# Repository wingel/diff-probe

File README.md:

What is different in this fork?
===============================
* KiCAD version of only the tested B variant
* Board slightly optimized (NF resistors removed)
* JLCPCB production files added (with assembly)

An almost GHZ active differential probe
=======================================

This is the design for an active differential probe which has a
bandwidth of about 800MHz and which is useful to beyond 1GHz.

I have written some articles about the probe:
[Part&nbsp;1](http://blog.weinigel.se/2016/02/26/ghz-differential-probe.html),
[Part&nbsp;2](http://blog.weinigel.se/2016/02/28/ghz-differential-probe-2.html), and
[Part&nbsp;3](http://blog.weinigel.se/2016/03/16/ghz-differential-probe-3.html).

A few notes
===========

So far I have only built the B variant of the probe, that is, the
probe with separate OP amps for the inputs.

On variant B, the input resistors R20/R21, R28/R29 and output
resistors R30/R31 are arranged in such a way that one can use just one
resistor between the input of the first resistor to the output of the
second resistor.  That's why it says "0Ω/NF" on one of the resistors
in both pairs.

The image in [S21ProbeBW_1.png](S21ProbeBW_1.png) shows a plot of the
frequency response for variant B using LMH6702 OP-AMPs, 150Ω on R20
and R28, 220Ω on R26, R27, R37 and R38 and 1.1k on R22 and R32.  Note
that the 150Ω resistors were mounted across R20/R21 and R28/R29 and
the and 50Ω matching resistor for the output was mounted across
R30/R31.  The power supply with a LMH6702 OP-AMPs should be about 5V
and the probe should be able to measure signals up to about +/-3.3V.

If you want the probe input to be AC coupled you can mount the input
resistor in its proper position on R20 and R28 and mount a capacitor
(0.1µF might be a good starting value) on R21 and R29.  You can also
AC couple the output by mounting the 50Ω matching resistor on R30 and
a another small capacitor on R31.

License
=======

[diff-probe](https://github.com/wingel/diff-probe) by
[Christer Weinigel](mailto:christer@weinigel.se) is licensed under a
[Creative Commons Attribution 4.0 International
License](http://creativecommons.org/licenses/by/4.0/).

The intent is to make this PCB available to anyone that finds it
useful as long as I get credit for the original design.  If you want
to use the design and have issues with the above license, please
contact me.

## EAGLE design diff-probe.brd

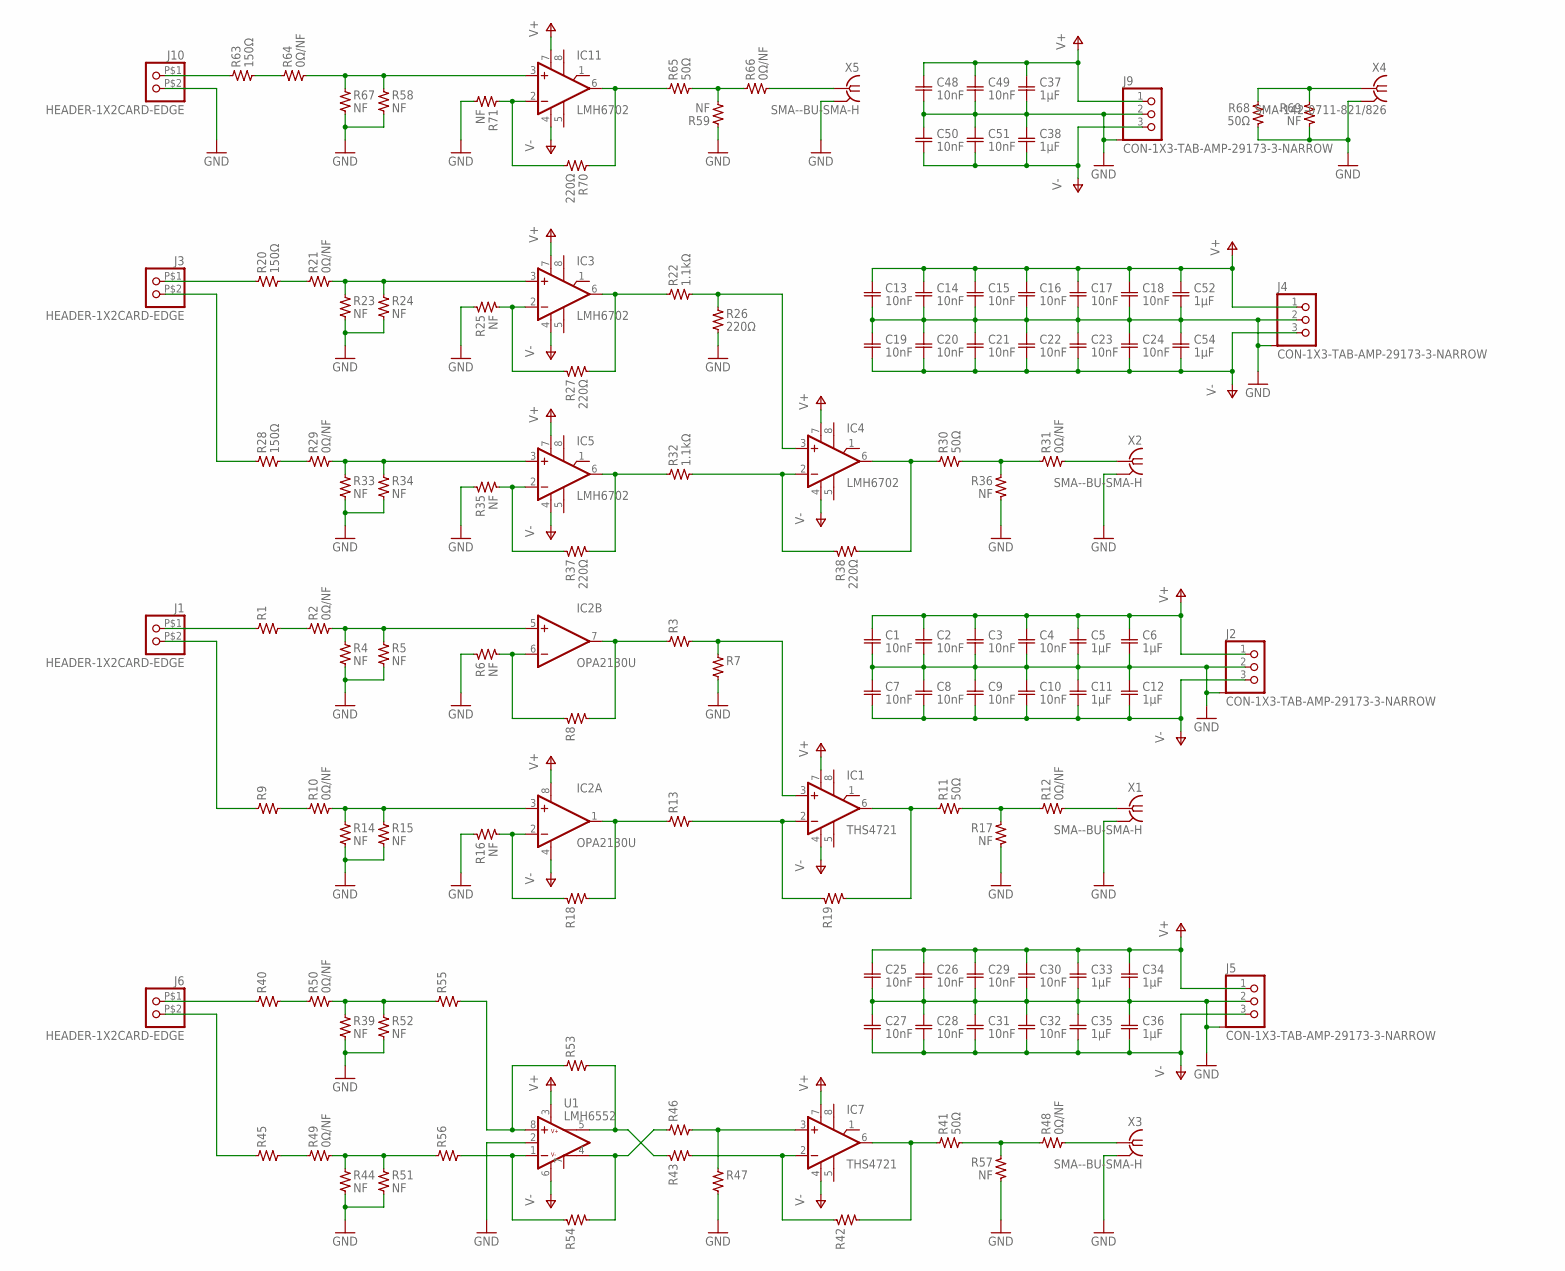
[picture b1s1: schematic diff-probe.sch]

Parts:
C1, C2, C3, C4, C7, C8, C9, C10, C13, C14, C15, C16, C17, C18, C19, C20, C21, C22, C23, C24, C25, C26, C27, C28, C29, C30, C31, C32, C48, C49, C50, C51: 10nF; 0402-SQUARE
C5, C6, C11, C12, C33, C34, C35, C36, C37, C38: 1µF; 0603-SQUARE
C52, C54: 1µF; 0603
IC1, IC7: THS4721; SO08
IC2: OPA2130U; SO08
IC3, IC4, IC5, IC11: LMH6702; SO08
J1, J3, J6, J10: HEADER-1X2CARD-EDGE; CARD_EDGE_PADS-1X2
J2, J4, J5, J9: CON-1X3-TAB-AMP-29173-3-NARROW; AMP-29173-3-NARROW
R1, R3, R7, R8, R9, R13, R18, R19, R40, R42, R43, R45, R46, R47, R53, R54, R55, R56: R-US-0402-SQUARE; 0402-SQUARE
R2, R10, R12, R21, R29, R31, R48, R49, R50, R64, R66: 0Ω/NF; 0402-SQUARE
R4, R5, R6, R14, R15, R16, R17, R23, R24, R25, R33, R34, R35, R36, R39, R44, R51, R52, R57, R58, R59, R67, R71: NF; 0402-SQUARE
R11, R30, R41, R65, R68: 50Ω; 0402-SQUARE
R20, R28, R63: 150Ω; 0402-SQUARE
R22, R32: 1.1kΩ; 0402-SQUARE
R26, R27, R37, R38, R70: 220Ω; 0402-SQUARE
R69: NF; 0603-SQUARE
U1: LMH6552; SO08
X1, X2, X3, X5: SMA--BU-SMA-H; BU-SMA-H
X4: SMA-142-0711-821/826; J502-ND-142-0711-821/826

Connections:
GND: C1.P$2 (2), C2.P$2 (2), C3.P$2 (2), C4.P$2 (2), C5.2, C6.2, C7.P$1 (1), C8.P$1 (1), C9.P$1 (1), C10.P$1 (1), C11.1, C12.1, C13.P$2 (2), C14.P$2 (2), C15.P$2 (2), C16.P$2 (2), C17.P$2 (2), C18.P$2 (2), C19.P$1 (1), C20.P$1 (1), C21.P$1 (1), C22.P$1 (1), C23.P$1 (1), C24.P$1 (1), C25.P$2 (2), C26.P$2 (2), C27.P$1 (1), C28.P$1 (1), C29.P$2 (2), C30.P$2 (2), C31.P$1 (1), C32.P$1 (1), C33.2, C34.2, C35.1, C36.1, C37.2, C38.1, C48.P$2 (2), C49.P$2 (2), C50.P$1 (1), C51.P$1 (1), C52.2, C54.1, J2.2, J2.P$4, J2.P$5, J4.2, J4.P$4, J4.P$5, J5.2, J5.P$4, J5.P$5, J9.2, J9.P$4, J9.P$5, J10.P$2 (2), R4.P$2 (2), R5.P$2 (2), R6.P$1 (1), R7.P$2 (2), R14.P$2 (2), R15.P$2 (2), R16.P$1 (1), R17.P$2 (2), R23.P$2 (2), R24.P$2 (2), R25.P$1 (1), R26.P$2 (2), R33.P$2 (2), R34.P$2 (2), R35.P$1 (1), R36.P$2 (2), R39.P$2 (2), R44.P$2 (2), R47.P$2 (2), R51.P$2 (2), R52.P$2 (2), R57.P$2 (2), R58.P$2 (2), R59.P$1 (1), R67.P$2 (2), R68.P$2 (2), R69.2, R71.P$2 (2), U1.2 (VCM), X1.2, X1.3 (2), X1.4 (2), X1.5 (2), X2.2, X2.3 (2), X2.4 (2), X2.5 (2), X3.2, X3.3 (2), X3.4 (2), X3.5 (2), X4.G@1 (2), X4.G@2 (2), X4.G@3 (2), X4.G@4 (2), X5.2, X5.3 (2), X5.4 (2), X5.5 (2)
unnamed: IC11.3 (+IN), R58.P$1 (1), R64.P$2 (2), R67.P$1 (1)
unnamed: R63.P$2 (2), R64.P$1 (1)
unnamed: J10.P$1 (1), R63.P$1 (1)
unnamed: R59.P$2 (2), R65.P$2 (2), R66.P$1 (1)
unnamed: IC11.6 (OUT), R65.P$1 (1), R70.P$1 (1)
unnamed: R66.P$2 (2), X5.1
unnamed: R53.P$1 (1), R55.P$2 (2), U1.8 (+IN)
unnamed: R40.P$2 (2), R50.P$1 (1)
unnamed: R43.P$1 (1), R53.P$2 (2), U1.5 (-OUT)
unnamed: R41.P$2 (2), R48.P$1 (1), R57.P$1 (1)
unnamed: IC7.6 (OUT), R41.P$1 (1), R42.P$2 (2)
unnamed: IC7.2 (-IN), R42.P$1 (1), R43.P$2 (2)
unnamed: R39.P$1 (1), R50.P$2 (2), R52.P$1 (1), R55.P$1 (1)
unnamed: R45.P$2 (2), R49.P$1 (1)
unnamed: R46.P$1 (1), R54.P$2 (2), U1.4 (+OUT)
unnamed: IC7.3 (+IN), R46.P$2 (2), R47.P$1 (1)
unnamed: J6.P$1 (1), R40.P$1 (1)
unnamed: J6.P$2 (2), R45.P$1 (1)
unnamed: R48.P$2 (2), X3.1
unnamed: R54.P$1 (1), R56.P$2 (2), U1.1 (-IN)
unnamed: R44.P$1 (1), R49.P$2 (2), R51.P$1 (1), R56.P$1 (1)
unnamed: IC11.2 (-IN), R70.P$2 (2), R71.P$1 (1)
unnamed: R68.P$1 (1), R69.1, X4.1
unnamed: IC2.5 (+IN), R2.P$2 (2), R4.P$1 (1), R5.P$1 (1)
unnamed: R1.P$2 (2), R2.P$1 (1)
unnamed: IC2.7 (OUT), R3.P$1 (1), R8.P$2 (2)
unnamed: IC3.3 (+IN), R21.P$2 (2), R23.P$1 (1), R24.P$1 (1)
unnamed: R20.P$2 (2), R21.P$1 (1)
unnamed: IC3.6 (OUT), R22.P$1 (1), R27.P$2 (2)
unnamed: R11.P$2 (2), R12.P$1 (1), R17.P$1 (1)
unnamed: R30.P$2 (2), R31.P$1 (1), R36.P$1 (1)
unnamed: IC4.6 (OUT), R30.P$1 (1), R38.P$2 (2)
unnamed: IC4.2 (-IN), R32.P$2 (2), R38.P$1 (1)
unnamed: IC5.3 (+IN), R29.P$2 (2), R33.P$1 (1), R34.P$1 (1)
unnamed: R28.P$2 (2), R29.P$1 (1)
unnamed: R12.P$2 (2), X1.1
unnamed: IC5.6 (OUT), R32.P$1 (1), R37.P$2 (2)
unnamed: IC4.3 (+IN), R22.P$2 (2), R26.P$1 (1)
unnamed: J3.P$1 (1), R20.P$1 (1)
unnamed: J3.P$2 (2), R28.P$1 (1)
unnamed: IC1.6 (OUT), R11.P$1 (1), R19.P$2 (2)
unnamed: IC1.2 (-IN), R13.P$2 (2), R19.P$1 (1)
unnamed: IC2.3 (+IN), R10.P$2 (2), R14.P$1 (1), R15.P$1 (1)
unnamed: R9.P$2 (2), R10.P$1 (1)
unnamed: IC2.1 (OUT), R13.P$1 (1), R18.P$2 (2)
unnamed: IC1.3 (+IN), R3.P$2 (2), R7.P$1 (1)
unnamed: J1.P$1 (1), R1.P$1 (1)
unnamed: J1.P$2 (2), R9.P$1 (1)
unnamed: IC2.2 (-IN), R16.P$2 (2), R18.P$1 (1)
unnamed: R31.P$2 (2), X2.1
unnamed: IC2.6 (-IN), R6.P$2 (2), R8.P$1 (1)
unnamed: IC5.2 (-IN), R35.P$2 (2), R37.P$1 (1)
unnamed: IC3.2 (-IN), R25.P$2 (2), R27.P$1 (1)
V+: C1.P$1 (1), C2.P$1 (1), C3.P$1 (1), C4.P$1 (1), C5.1, C6.1, C13.P$1 (1), C14.P$1 (1), C15.P$1 (1), C16.P$1 (1), C17.P$1 (1), C18.P$1 (1), C25.P$1 (1), C26.P$1 (1), C29.P$1 (1), C30.P$1 (1), C33.1, C34.1, C37.1, C48.P$1 (1), C49.P$1 (1), C52.1, IC1.7 (+VS1), IC2.8 (V+), IC3.7 (+VS1), IC4.7 (+VS1), IC5.7 (+VS1), IC7.7 (+VS1), IC11.7 (+VS1), J2.1, J4.1, J5.1, J9.1, U1.3 (V+)
V-: C7.P$2 (2), C8.P$2 (2), C9.P$2 (2), C10.P$2 (2), C11.2, C12.2, C19.P$2 (2), C20.P$2 (2), C21.P$2 (2), C22.P$2 (2), C23.P$2 (2), C24.P$2 (2), C27.P$2 (2), C28.P$2 (2), C31.P$2 (2), C32.P$2 (2), C35.2, C36.2, C38.2, C50.P$2 (2), C51.P$2 (2), C54.2, IC1.4 (-VS1), IC2.4 (V-), IC3.4 (-VS1), IC4.4 (-VS1), IC5.4 (-VS1), IC7.4 (-VS1), IC11.4 (-VS1), J2.3, J4.3, J5.3, J9.3, U1.6 (V-)

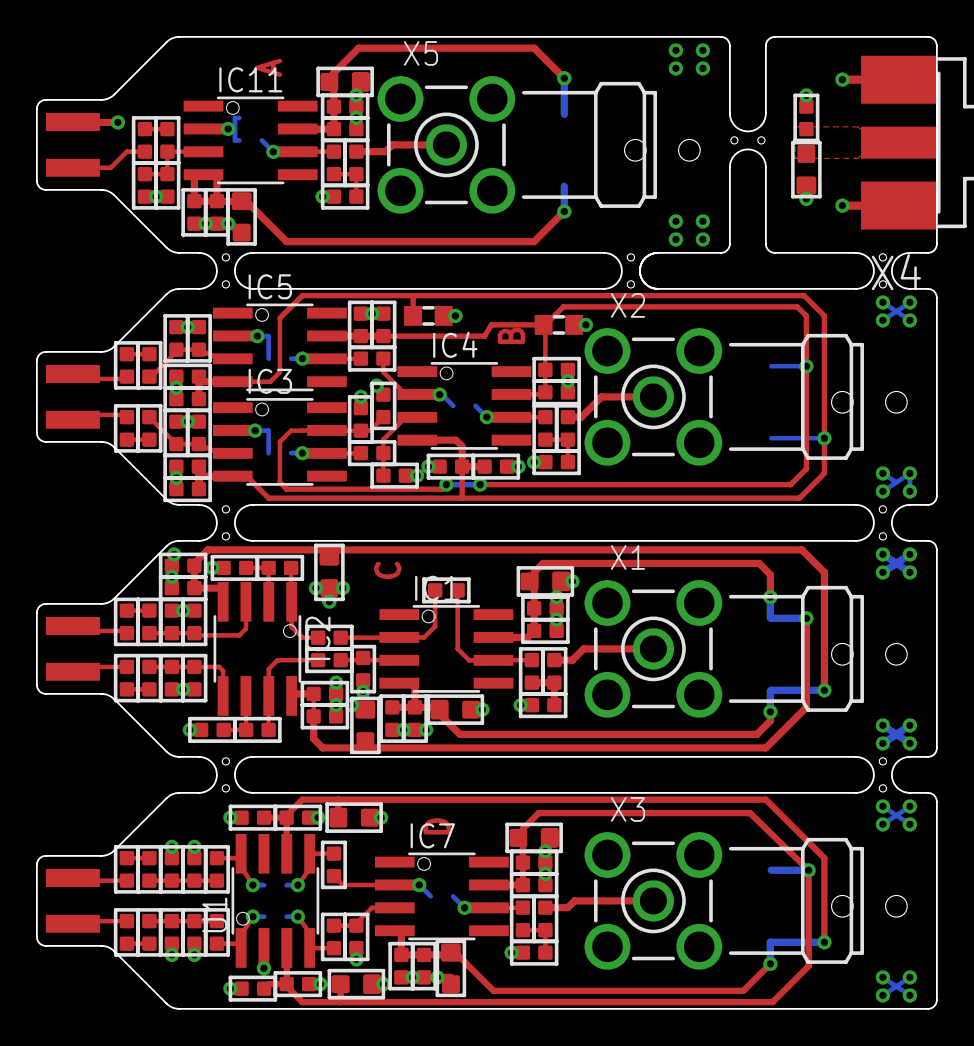
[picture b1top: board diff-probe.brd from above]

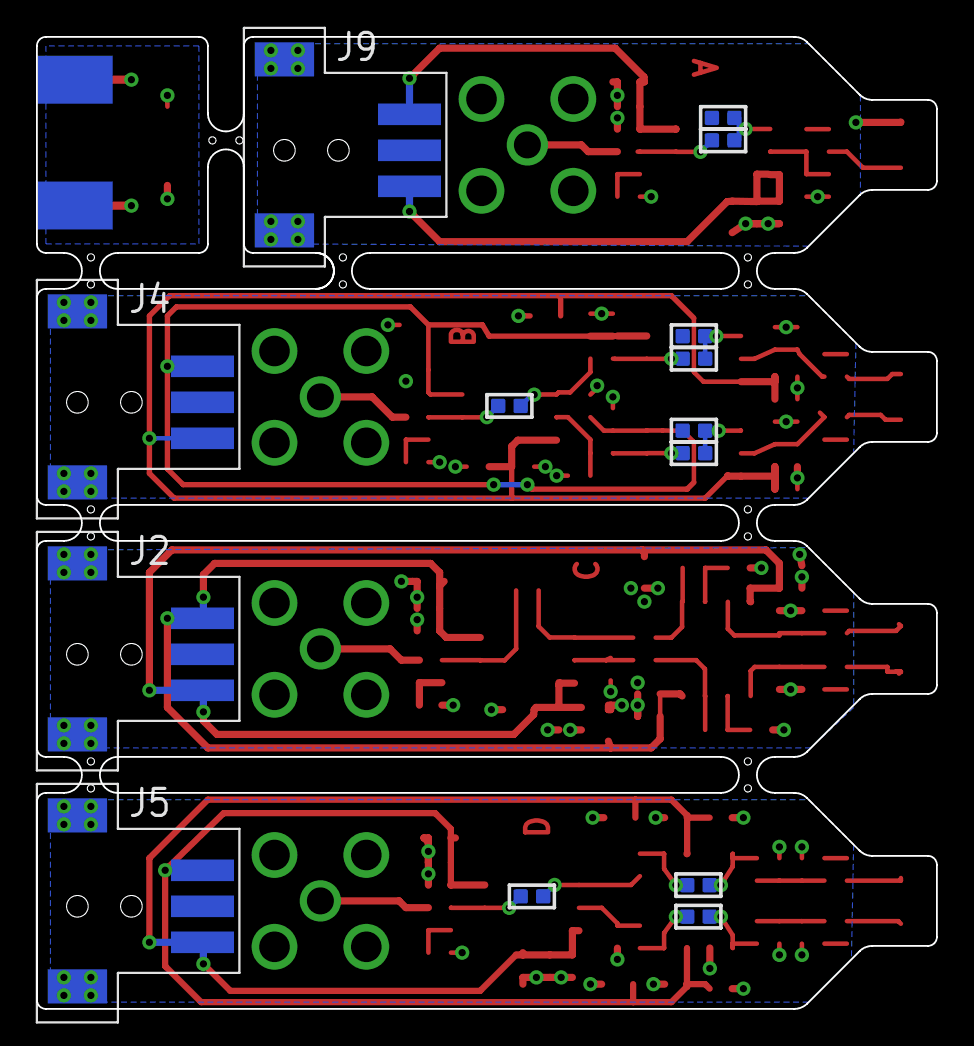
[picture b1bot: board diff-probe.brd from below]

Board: 2 copper layers, 50.0 x 54.0 mm, 133 parts (14 on the bottom side), 56 nets.

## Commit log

2016-03-31 Create repository
2016-03-31 Add README.md
2016-03-31 Add plot of probe bandwith
2016-03-31 Add eagle files for diff probe
2017-05-15 Add PDF of schematics
2017-05-15 Add "Variant" text to schematics.
2021-12-08 add basic kicad version
2021-12-08 Remove NF resistors and add LCSC part numbers
2021-12-08 remove NF resistors and rotate input resistors
2021-12-08 use a better SMA connector
2021-12-08 add JLCPCB production files
2021-12-08 fix DRC (edge cuts and closeness of trace to letter)
2021-12-08 tidy schematic
2022-01-15 give nets names to make the PCB more readable
2022-01-15 optimize output
